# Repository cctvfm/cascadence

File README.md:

# cascadence
Cascadence is a low-cost eurorack-compatible Arduino development platform developed with the Modular Seattle Team.

`/hardware` contains the board and panel files

`/firmware` contains the released firmwares available. You can upload new firmwares using Arduino

`/software` contains the files and instructions needed to get Cascadence working with Arduino

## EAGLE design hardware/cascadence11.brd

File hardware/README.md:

Sch and Brd files created in Eagle 9.1.2.

Panel artwork created by Rae Lohse

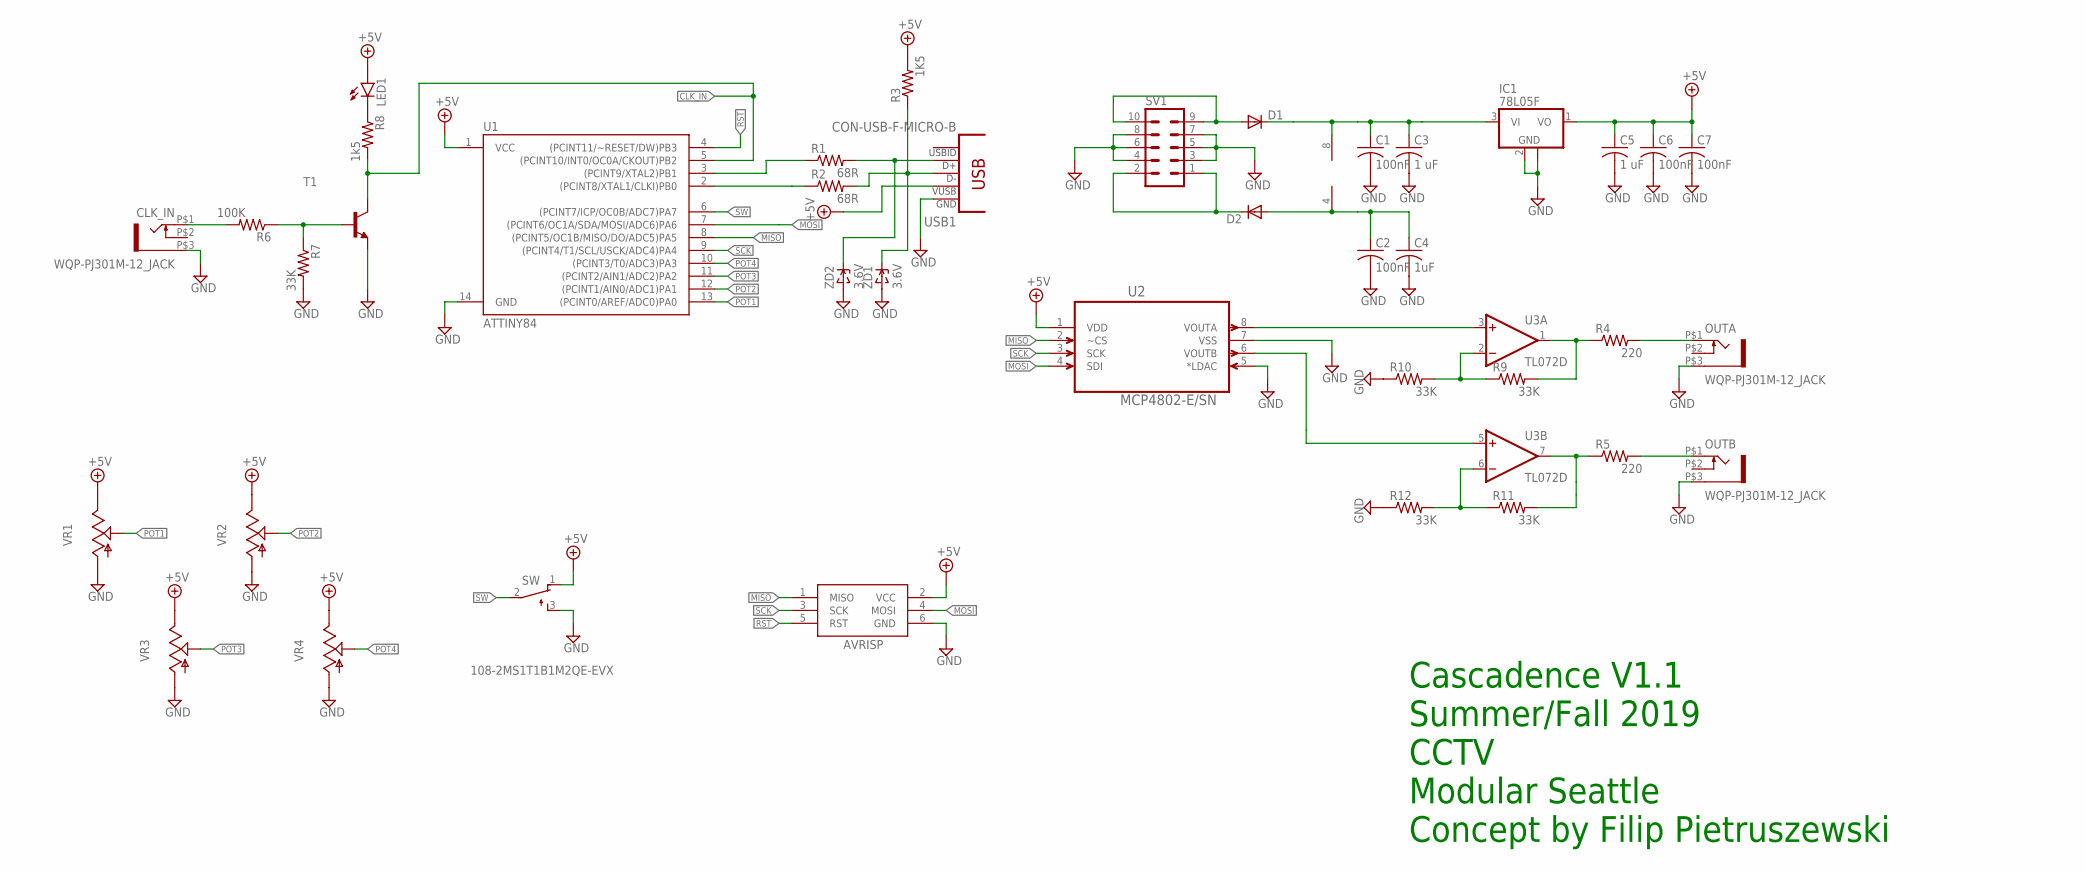
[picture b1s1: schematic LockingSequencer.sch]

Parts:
AVRISP: AVRISP-6; AVRISP
C1, C2, C6, C7: 100nF; C0805K
C3, C5: 1 uF; C1206
C4: 1uF; C1206
CLK_IN: WQP-PJ301M-12_JACK
D1, D2: DIODE-SMB; SMB
IC1: 78L05F; SOT89
LED1: LED3MM
OUTA: WQP-PJ301M-12_JACK
OUTB: WQP-PJ301M-12_JACK
R1, R2: 68R; R0805W
R3: 1K5; R0805W
R4, R5: 220; R0805W
R6: 100K; R0805W
R7, R9, R10, R11, R12: 33K; R0805W
R8: 1k5; R0805W
SV1: EURO_POWER_HEADERFAT_PADS; EURO_PWR_HEADER_FAT
SW: 108-2MS1T1B1M2QE-EVX; TL3XPO
T1: MMBT3904LT1-NPN-SOT23-BEC; SOT23-BEC
U1: ATTINY84; SO14
U2: MCP4802-E/SN; SOIC127P600X175-8N
U3: TL072D; SO08
USB1: CON-USB-F-MICRO-B; CONN_USB_MICRO-B
VR1, VR2, VR3, VR4: 9MM_SNAP-IN_POT_; 9MM_SNAP-IN_POT
ZD1, ZD2: 3.6V; SOD-123

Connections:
+5V: AVRISP.2 (VCC), C5.1, C6.1, C7.1, IC1.1 (VO), LED1.A, R3.2, SW.1 (O), U1.1 (VCC), U2.1 (VDD), USB1.P1 (VUSB), VR1.3 (E), VR2.3 (E), VR3.3 (E), VR4.3 (E)
CLK_IN: R8.2, T1.C, U1.5 ((PCINT10/INT0/OC0A/CKOUT)PB2)
GND: AVRISP.6 (GND), C1.2, C2.2, C3.2, C4.2, C5.2, C6.2, C7.2, CLK_IN.P$3 (1), IC1.2 (GND), IC1.2@1 (GND), OUTA.P$3 (1), OUTB.P$3 (1), R7.2, R10.1, R12.1, SV1.3, SV1.4, SV1.5, SV1.6, SV1.7, SV1.8, SW.3 (S), T1.E, U1.14 (GND), U2.5 (*LDAC), U2.7 (VSS), USB1.P5 (GND), VR1.1 (A), VR2.1 (A), VR3.1 (A), VR4.1 (A), ZD1.A, ZD2.A
MISO: AVRISP.1 (MISO), U1.8 ((PCINT5/OC1B/MISO/DO/ADC5)PA5), U2.2 (~CS)
MOSI: AVRISP.4 (MOSI), U1.7 ((PCINT6/OC1A/SDA/MOSI/ADC6)PA6), U2.4 (SDI)
unnamed: R1.2, USB1.P3 (D+), ZD2.C
unnamed: R2.2, R3.1, USB1.P2 (D-), ZD1.C
unnamed: R2.1, U1.2 ((PCINT8/XTAL1/CLKI)PB0)
unnamed: U2.8 (VOUTA), U3.3 (+IN)
unnamed: R1.1, U1.3 ((PCINT9/XTAL2)PB1)
unnamed: D2.C, SV1.1, SV1.2
unnamed: U2.6 (VOUTB), U3.5 (+IN)
unnamed: R4.1, R9.2, U3.1 (OUT)
unnamed: R5.1, R11.2, U3.7 (OUT)
unnamed: CLK_IN.P$1 (2), R6.2
unnamed: OUTA.P$1 (2), R4.2
unnamed: OUTB.P$1 (2), R5.2
unnamed: R6.1, R7.1, T1.B
unnamed: C2.1, C4.1, D2.A, U3.4 (V-)
unnamed: LED1.K (C), R8.1
unnamed: D1.A, SV1.9, SV1.10
unnamed: C1.1, C3.1, D1.C, IC1.3 (VI), U3.8 (V+)
unnamed: R9.1, R10.2, U3.2 (-IN)
unnamed: R11.1, R12.2, U3.6 (-IN)
POT1: U1.13 ((PCINT0/AREF/ADC0)PA0), VR1.2 (S)
POT2: U1.12 ((PCINT1/AIN0/ADC1)PA1), VR2.2 (S)
POT3: U1.11 ((PCINT2/AIN1/ADC2)PA2), VR3.2 (S)
POT4: U1.10 ((PCINT3/T0/ADC3)PA3), VR4.2 (S)
RST: AVRISP.5 (RST), U1.4 ((PCINT11/~RESET/DW)PB3)
SCK: AVRISP.3 (SCK), U1.9 ((PCINT4/T1/SCL/USCK/ADC4)PA4), U2.3 (SCK)
SW: SW.2, U1.6 ((PCINT7/ICP/OC0B/ADC7)PA7)

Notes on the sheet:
Cascadence V1.1 Summer/Fall 2019 CCTV Modular Seattle Concept by Filip Pietruszewski

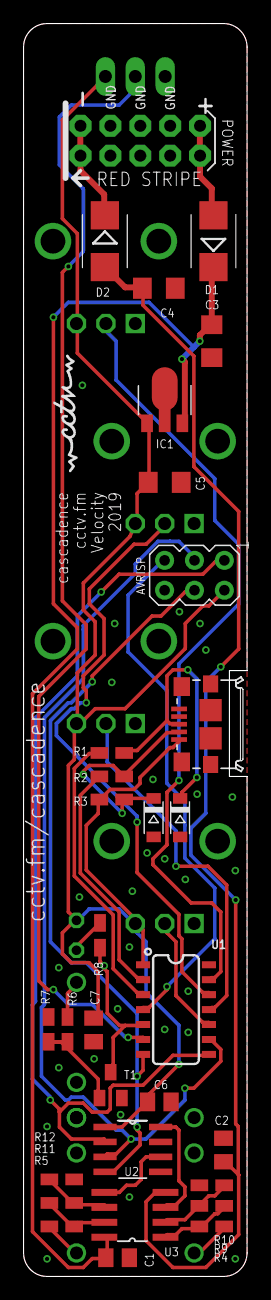
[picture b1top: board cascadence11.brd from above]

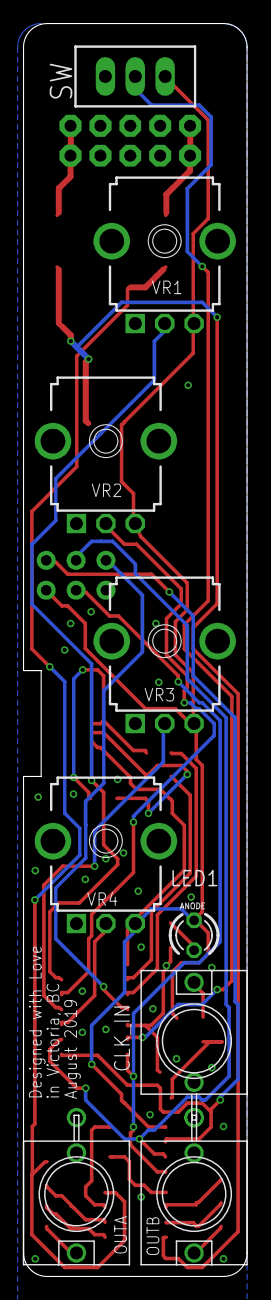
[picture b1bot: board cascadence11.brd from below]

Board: 2 copper layers, 19.0 x 106.5 mm, 40 parts (9 on the bottom side), 31 nets.

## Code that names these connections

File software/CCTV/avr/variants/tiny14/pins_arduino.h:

/*
  pins_arduino.c - pin definitions for the Arduino board
  Part of Arduino / Wiring Lite

  Copyright (c) 2005 David A. Mellis

  This library is free software; you can redistribute it and/or
  modify it under the terms of the GNU Lesser General Public
  License as published by the Free Software Foundation; either
  version 2.1 of the License, or (at your option) any later version.

  This library is distributed in the hope that it will be useful,
  but WITHOUT ANY WARRANTY; without even the implied warranty of
  MERCHANTABILITY or FITNESS FOR A PARTICULAR PURPOSE.  See the GNU
  Lesser General Public License for more details.

  You should have received a copy of the GNU Lesser General
  Public License along with this library; if not, write to the
  Free Software Foundation, Inc., 59 Temple Place, Suite 330,
  Boston, MA  02111-1307  USA

  $Id: pins_arduino.c 565 2009-03-25 10:50:00Z dmellis $

  Modified 28-08-2009 for attiny84 R.Wiersma
  Modified 09-10-2009 for attiny45 A.Saporetti
*/

#ifndef Pins_Arduino_h
#define Pins_Arduino_h

#include <avr/pgmspace.h>

// ATMEL ATTINY84 / ARDUINO
//
//                           +-\/-+
//                     VCC  1|    |14  GND
//             (D 10)  PB0  2|    |13  AREF (D  0)
//             (D  9)  PB1  3|    |12  PA1  (D  1)
//                     PB3  4|    |11  PA2  (D  2)
//  PWM  INT0  (D  8)  PB2  5|    |10  PA3  (D  3)
//  PWM        (D  7)  PA7  6|    |9   PA4  (D  4)
//  PWM        (D  6)  PA6  7|    |8   PA5  (D  5)        PWM
//                           +----+

const static uint8_t A0 = 0;
const static uint8_t A1 = 1;
const static uint8_t A2 = 2;
const static uint8_t A3 = 3;
const static uint8_t A4 = 4;
const static uint8_t A5 = 5;
const static uint8_t A6 = 6;
const static uint8_t A7 = 7;

#define digitalPinToPCICR(p)    ( ((p) >= 0 && (p) <= 10) ? (&GIMSK) : ((uint8_t *)0) )
#define digitalPinToPCICRbit(p) ( ((p) <= 7) ? PCIE0 : PCIE1 )
#define digitalPinToPCMSK(p)    ( ((p) <= 7) ? (&PCMSK0) : (((p) <= 10) ? (&PCMSK1) : ((uint8_t *)0)) )
#define digitalPinToPCMSKbit(p) ( ((p) <= 7) ? (p) : (10 - (p)) )

#ifdef ARDUINO_MAIN

// these arrays map port names (e.g. port B) to the
// appropriate addresses for various functions (e.g. reading
// and writing)
const uint16_t PROGMEM port_to_mode_PGM[] =
{
  NOT_A_PORT,
  (uint16_t)&DDRA,
  (uint16_t)&DDRB,
};

const uint16_t PROGMEM port_to_output_PGM[] =
{
  NOT_A_PORT,
  (uint16_t)&PORTA,
  (uint16_t)&PORTB,
};

const uint16_t PROGMEM port_to_input_PGM[] =
{
  NOT_A_PORT,
  (uint16_t)&PINA,
  (uint16_t)&PINB,
};

const uint8_t PROGMEM digital_pin_to_port_PGM[] =
{
  PA, /* 0 */
  PA,
  PA,
  PA,
  PA,
  PA,
  PA,
  PA,
  PB, /* 8 */
  PB,
  PB,
};

const uint8_t PROGMEM digital_pin_to_bit_mask_PGM[] =
{
  _BV(0), /* port A */
  _BV(1),
  _BV(2),
  _BV(3),
  _BV(4),
  _BV(5),
  _BV(6),
  _BV(7),
  _BV(2), /* port B */
  _BV(1),
  _BV(0),
};

const uint8_t PROGMEM digital_pin_to_timer_PGM[] =
{
  NOT_ON_TIMER,
  NOT_ON_TIMER,
  NOT_ON_TIMER,
  NOT_ON_TIMER,
  NOT_ON_TIMER,
  TIMER1B, /* OC1B */
  TIMER1A, /* OC1A */
  TIMER0B, /* OC0B */
  TIMER0A, /* OC0A */
  NOT_ON_TIMER,
  NOT_ON_TIMER,
};

#endif

#endif

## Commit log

2019-10-03 Rename LockingSequencer.brd to cascadence11.brd
2019-10-03 Rename LockingSequencer.sch to cascadence11.sch
2019-10-09 Contributor Name Correction
    Corrected name of panel designer to Rae Lohse
2019-10-25 Implemented Chris's Improvement to parameter updates
    Changed the way we check for updates to the ADSR parameters. the 'checkforchange' function now sees if the pot has moved while you're on that channel, and only then does it change the ADSR.

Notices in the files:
parts and their libraries:
SparkFun-IC-Microcontroller: Licensing: Creative Commons ShareAlike 4.0 International - https://creativecommons.org/licenses/by-sa/4.0
